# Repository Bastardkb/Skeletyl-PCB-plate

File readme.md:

# Skeletyl PCB - plate

Flexible PCB made for the Skeletyl.

With per-key RGB.

This repository contains all files necessary to order a PCB.

If you want to modify the design files, the Kicad sources are included.
If you just want to order the PCBs, check out the Release section which contain the gerber files.

## How to order

Order with a 0.6mm or 0.8mm PCB thickness

## License

Licensed under CC BY-NC-SA 4.0
Copyright Quentin Lebastard 2021

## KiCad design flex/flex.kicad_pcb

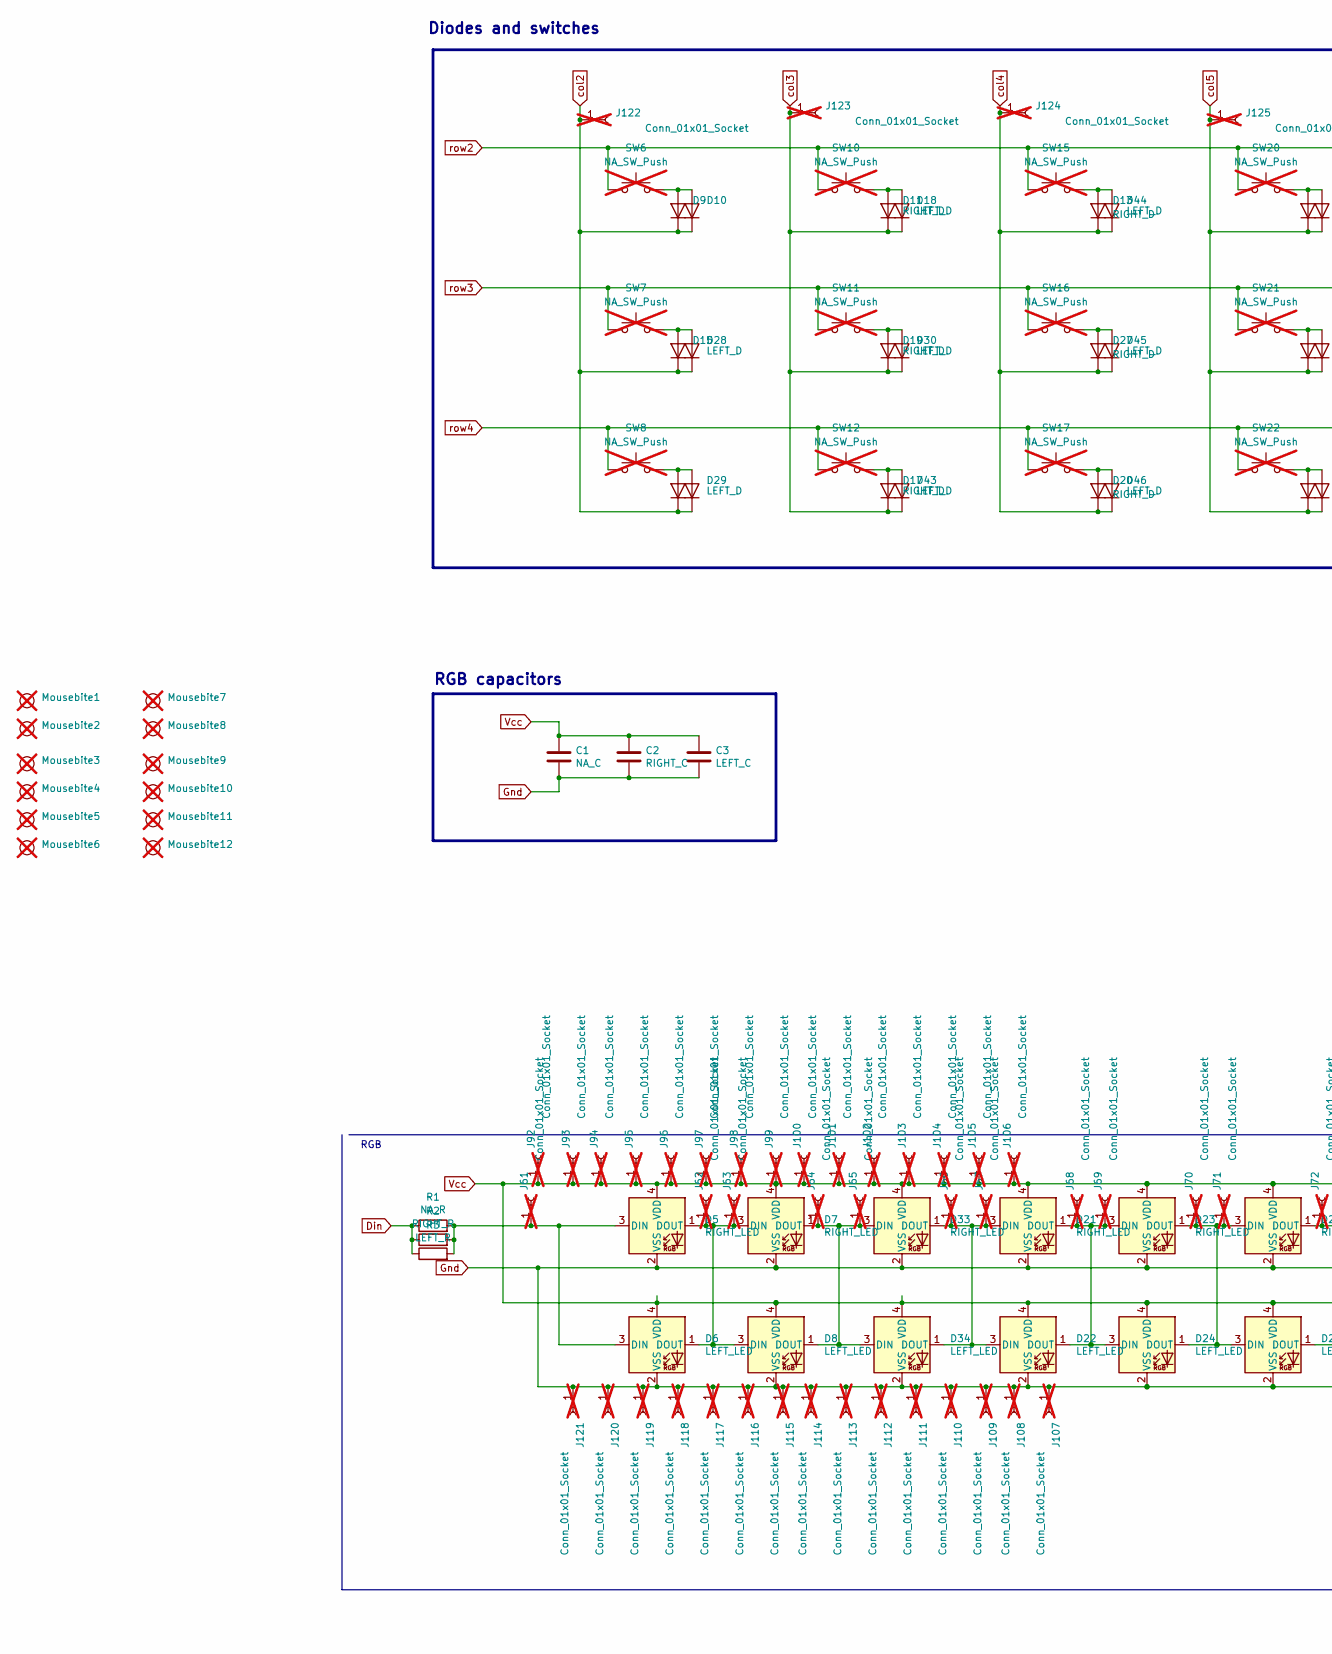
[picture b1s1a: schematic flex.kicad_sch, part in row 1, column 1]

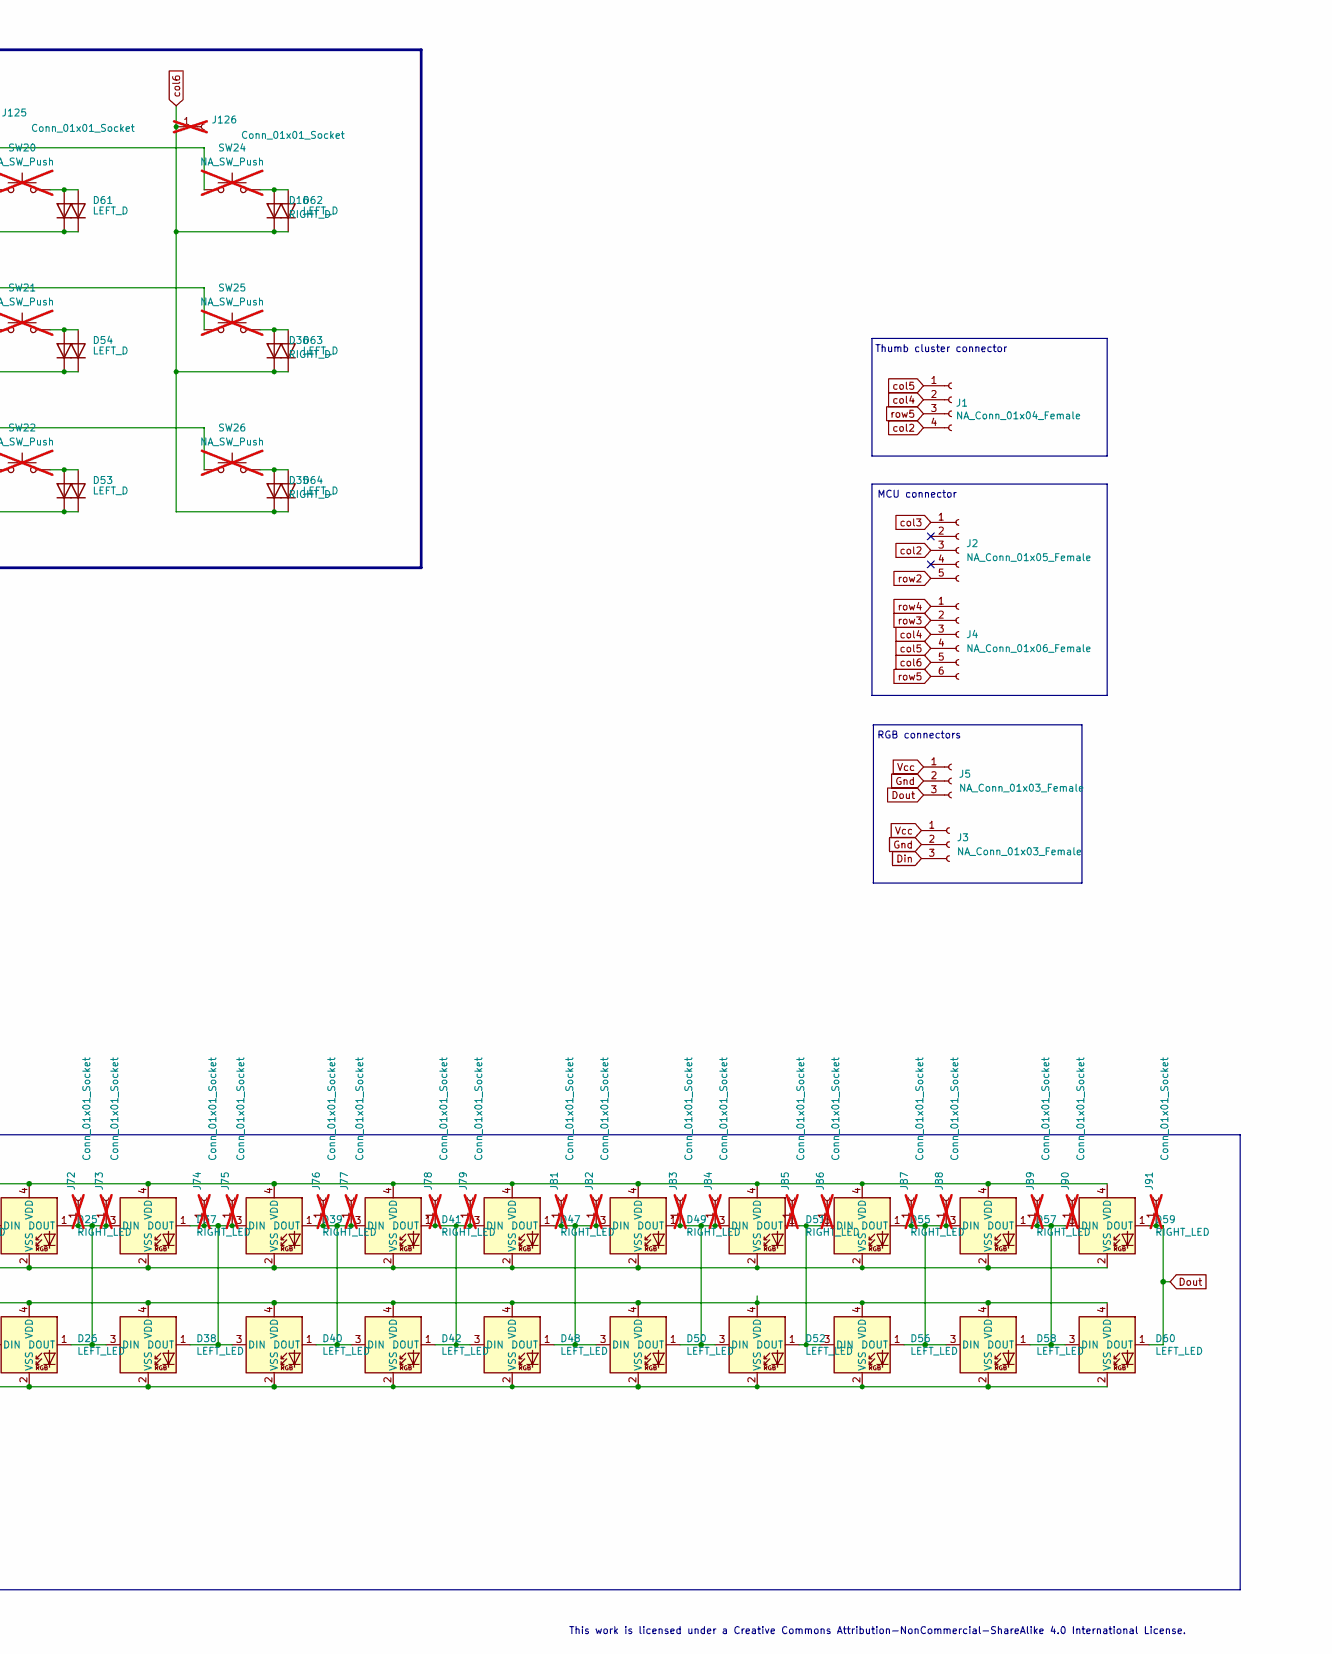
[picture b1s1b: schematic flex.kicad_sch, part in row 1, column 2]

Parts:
C1: NA_C; C_1206_3216Metric_Pad1.33x1.80mm_HandSolder_reversible
C2: RIGHT_C; R_0402
C3: LEFT_C; R_0402
D5, D7, D21, D23, D25, D33, D37, D39, D41, D47, D49, D51, D55, D57, D59: RIGHT_LED; SK6812_mini_e_corners
D6, D8, D22, D24, D26, D34, D38, D40, D42, D48, D50, D52, D56, D58, D60: LEFT_LED; SK6812_mini_e_corners_noedgecuts
D9, D11, D12, D13, D14, D15, D16, D17, D19, D20, D27, D31, D32, D35, D36: RIGHT_D; SOD123_assembly
D10, D18, D28, D29, D30, D43, D44, D45, D46, D53, D54, D61, D62, D63, D64: LEFT_D; SOD123_assembly
J1: NA_Conn_01x04_Female; PinHeader_1x04_P2.54mm_Vertical
J2: NA_Conn_01x05_Female; PinHeader_1x05_P2.54mm_Vertical
J3, J5: NA_Conn_01x03_Female; PinHeader_1x03_P2.54mm_Vertical
J4: NA_Conn_01x06_Female; PinHeader_1x06_P2.54mm_Vertical
J61, J63, J65, J67, J69, J71, J73, J75, J77, J79, J82, J84, J86, J88, J90: Conn_01x01_Socket; PinHeader_1x01_P1.27mm_Vertical_IN; not fitted
J62, J64, J66, J68, J70, J72, J74, J76, J78, J81, J83, J85, J87, J89, J91: Conn_01x01_Socket; PinHeader_1x01_P1.27mm_Vertical_OUT; not fitted
J92, J93, J94, J95, J96, J97, J98, J99, J100, J101, J102, J103, J104, J105, J106: Conn_01x01_Socket; PinHeader_1x01_P1.27mm_Vertical_VCC; not fitted
J107, J108, J109, J110, J111, J112, J113, J114, J115, J116, J117, J118, J119, J120, J121: Conn_01x01_Socket; PinHeader_1x01_P1.27mm_Vertical_GND; not fitted
J122, J123, J124, J125, J126: Conn_01x01_Socket; PinHeader_1x01_P1.27mm_Vertical; not fitted
Mousebite1, Mousebite2, Mousebite3, Mousebite4, Mousebite5, Mousebite6, Mousebite7, Mousebite8, Mousebite9, Mousebite10, Mousebite11, Mousebite12: mousebite; not fitted
R1: NA_R; R_1206_3216Metric_Pad1.30x1.75mm_HandSolder_reversible
R2: RIGHT_R; R_0402
R3: LEFT_R; R_0402
SW6, SW7, SW8, SW10, SW11, SW12, SW15, SW16, SW17, SW20, SW21, SW22, SW24, SW25, SW26: NA_SW_Push; SW_MX_reversible; not fitted

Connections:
Din: J3.3, R1.1, R2.1, R3.1
Dout: D59.1 (DOUT), D60.1 (DOUT), J5.3, J91.1
Gnd: C1.2, C2.2, C3.2, D5.2 (VSS), D6.2 (VSS), D7.2 (VSS), D8.2 (VSS), D21.2 (VSS), D22.2 (VSS), D23.2 (VSS), D24.2 (VSS), D25.2 (VSS), D26.2 (VSS), D33.2 (VSS), D34.2 (VSS), D37.2 (VSS), D38.2 (VSS), D39.2 (VSS), D40.2 (VSS), D41.2 (VSS), D42.2 (VSS), D47.2 (VSS), D48.2 (VSS), D49.2 (VSS), D50.2 (VSS), D51.2 (VSS), D52.2 (VSS), D55.2 (VSS), D56.2 (VSS), D57.2 (VSS), D58.2 (VSS), D59.2 (VSS), D60.2 (VSS), J3.2, J5.2, J107.1, J108.1, J109.1, J110.1, J111.1, J112.1, J113.1, J114.1, J115.1, J116.1, J117.1, J118.1, J119.1, J120.1, J121.1
unnamed: D5.3 (DIN), D6.3 (DIN), J61.1, R1.2, R2.2, R3.2
unnamed: D5.1 (DOUT), D6.1 (DOUT), D7.3 (DIN), D8.3 (DIN), J62.1, J63.1
unnamed: D9.2 (A), D10.2 (A), SW6.2
unnamed: D11.2 (A), D18.2 (A), SW10.2
unnamed: D12.2 (A), D29.2 (A), SW8.2
unnamed: D13.2 (A), D44.2 (A), SW15.2
unnamed: D14.2 (A), D61.2 (A), SW20.2
unnamed: D15.2 (A), D28.2 (A), SW7.2
unnamed: D16.2 (A), D62.2 (A), SW24.2
unnamed: D17.2 (A), D43.2 (A), SW12.2
unnamed: D19.2 (A), D30.2 (A), SW11.2
unnamed: D20.2 (A), D46.2 (A), SW17.2
unnamed: D21.3 (DIN), D22.3 (DIN), D33.1 (DOUT), D34.1 (DOUT), J66.1, J67.1
unnamed: D21.1 (DOUT), D22.1 (DOUT), D23.3 (DIN), D24.3 (DIN), J68.1, J69.1
unnamed: D23.1 (DOUT), D24.1 (DOUT), D25.3 (DIN), D26.3 (DIN), J70.1, J71.1
unnamed: D25.1 (DOUT), D26.1 (DOUT), D37.3 (DIN), D38.3 (DIN), J72.1, J73.1
unnamed: D27.2 (A), D45.2 (A), SW16.2
unnamed: D31.2 (A), D53.2 (A), SW22.2
unnamed: D32.2 (A), D54.2 (A), SW21.2
unnamed: D7.1 (DOUT), D8.1 (DOUT), D33.3 (DIN), D34.3 (DIN), J64.1, J65.1
unnamed: D35.2 (A), D64.2 (A), SW26.2
unnamed: D36.2 (A), D63.2 (A), SW25.2
unnamed: D37.1 (DOUT), D38.1 (DOUT), D39.3 (DIN), D40.3 (DIN), J74.1, J75.1
unnamed: D39.1 (DOUT), D40.1 (DOUT), D41.3 (DIN), D42.3 (DIN), J76.1, J77.1
unnamed: D41.1 (DOUT), D42.1 (DOUT), D47.3 (DIN), D48.3 (DIN), J78.1, J79.1
unnamed: D47.1 (DOUT), D48.1 (DOUT), D49.3 (DIN), D50.3 (DIN), J81.1, J82.1
unnamed: D49.1 (DOUT), D50.1 (DOUT), D51.3 (DIN), D52.3 (DIN), J83.1, J84.1
unnamed: D51.1 (DOUT), D52.1 (DOUT), D55.3 (DIN), D56.3 (DIN)
unnamed: D55.1 (DOUT), D56.1 (DOUT), D57.3 (DIN), D58.3 (DIN), J87.1, J88.1
unnamed: D57.1 (DOUT), D58.1 (DOUT), D59.3 (DIN), D60.3 (DIN), J89.1
Vcc: C1.1, C2.1, C3.1, D5.4 (VDD), D6.4 (VDD), D7.4 (VDD), D8.4 (VDD), D21.4 (VDD), D22.4 (VDD), D23.4 (VDD), D24.4 (VDD), D25.4 (VDD), D26.4 (VDD), D33.4 (VDD), D34.4 (VDD), D37.4 (VDD), D38.4 (VDD), D39.4 (VDD), D40.4 (VDD), D41.4 (VDD), D42.4 (VDD), D47.4 (VDD), D48.4 (VDD), D49.4 (VDD), D50.4 (VDD), D51.4 (VDD), D52.4 (VDD), D55.4 (VDD), D56.4 (VDD), D57.4 (VDD), D58.4 (VDD), D59.4 (VDD), D60.4 (VDD), J3.1, J5.1, J92.1, J93.1, J94.1, J95.1, J96.1, J97.1, J98.1, J99.1, J100.1, J101.1, J102.1, J103.1, J104.1, J105.1, J106.1
col2: D9.1 (K), D10.1 (K), D12.1 (K), D15.1 (K), D28.1 (K), D29.1 (K), J1.4, J2.3, J122.1
col3: D11.1 (K), D17.1 (K), D18.1 (K), D19.1 (K), D30.1 (K), D43.1 (K), J2.1, J123.1
col4: D13.1 (K), D20.1 (K), D27.1 (K), D44.1 (K), D45.1 (K), D46.1 (K), J1.2, J4.3, J124.1
col5: D14.1 (K), D31.1 (K), D32.1 (K), D53.1 (K), D54.1 (K), D61.1 (K), J1.1, J4.4, J125.1
col6: D16.1 (K), D35.1 (K), D36.1 (K), D62.1 (K), D63.1 (K), D64.1 (K), J4.5, J126.1
row2: J2.5, SW6.1, SW10.1, SW15.1, SW20.1, SW24.1
row3: J4.2, SW7.1, SW11.1, SW16.1, SW21.1, SW25.1
row4: J4.1, SW8.1, SW12.1, SW17.1, SW22.1, SW26.1
row5: J1.3, J4.6

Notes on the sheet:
RGB connectors
MCU connector
Thumb cluster connector
RGB capacitors
Diodes and switches
RGB
This work is licensed under a Creative Commons Attribution-NonCommercial-ShareAlike 4.0 International License.

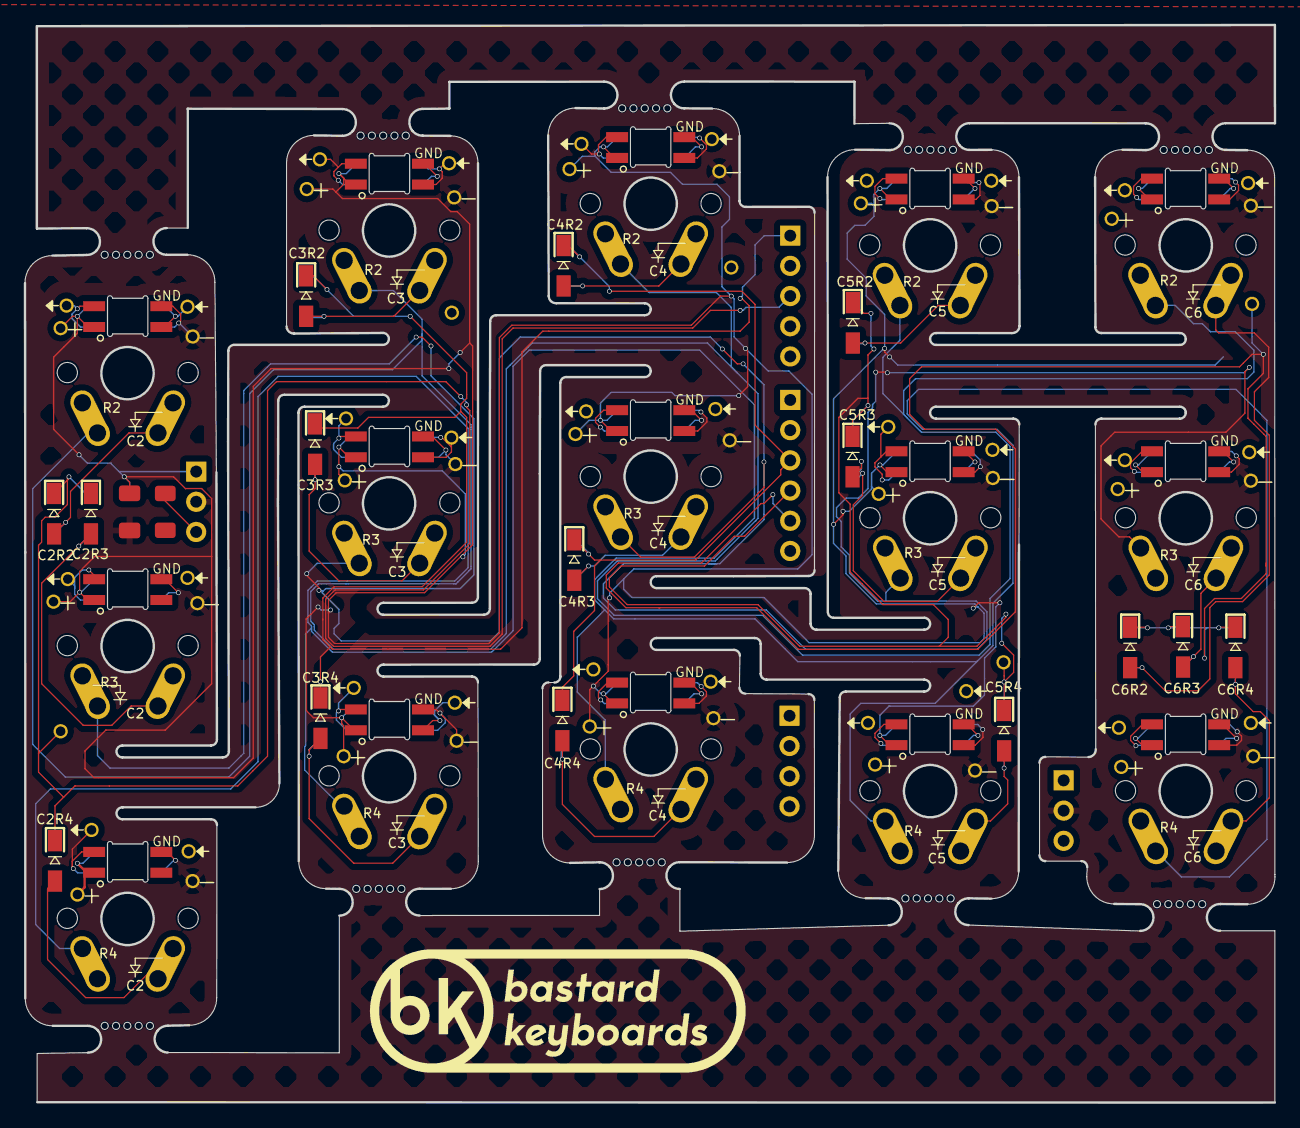
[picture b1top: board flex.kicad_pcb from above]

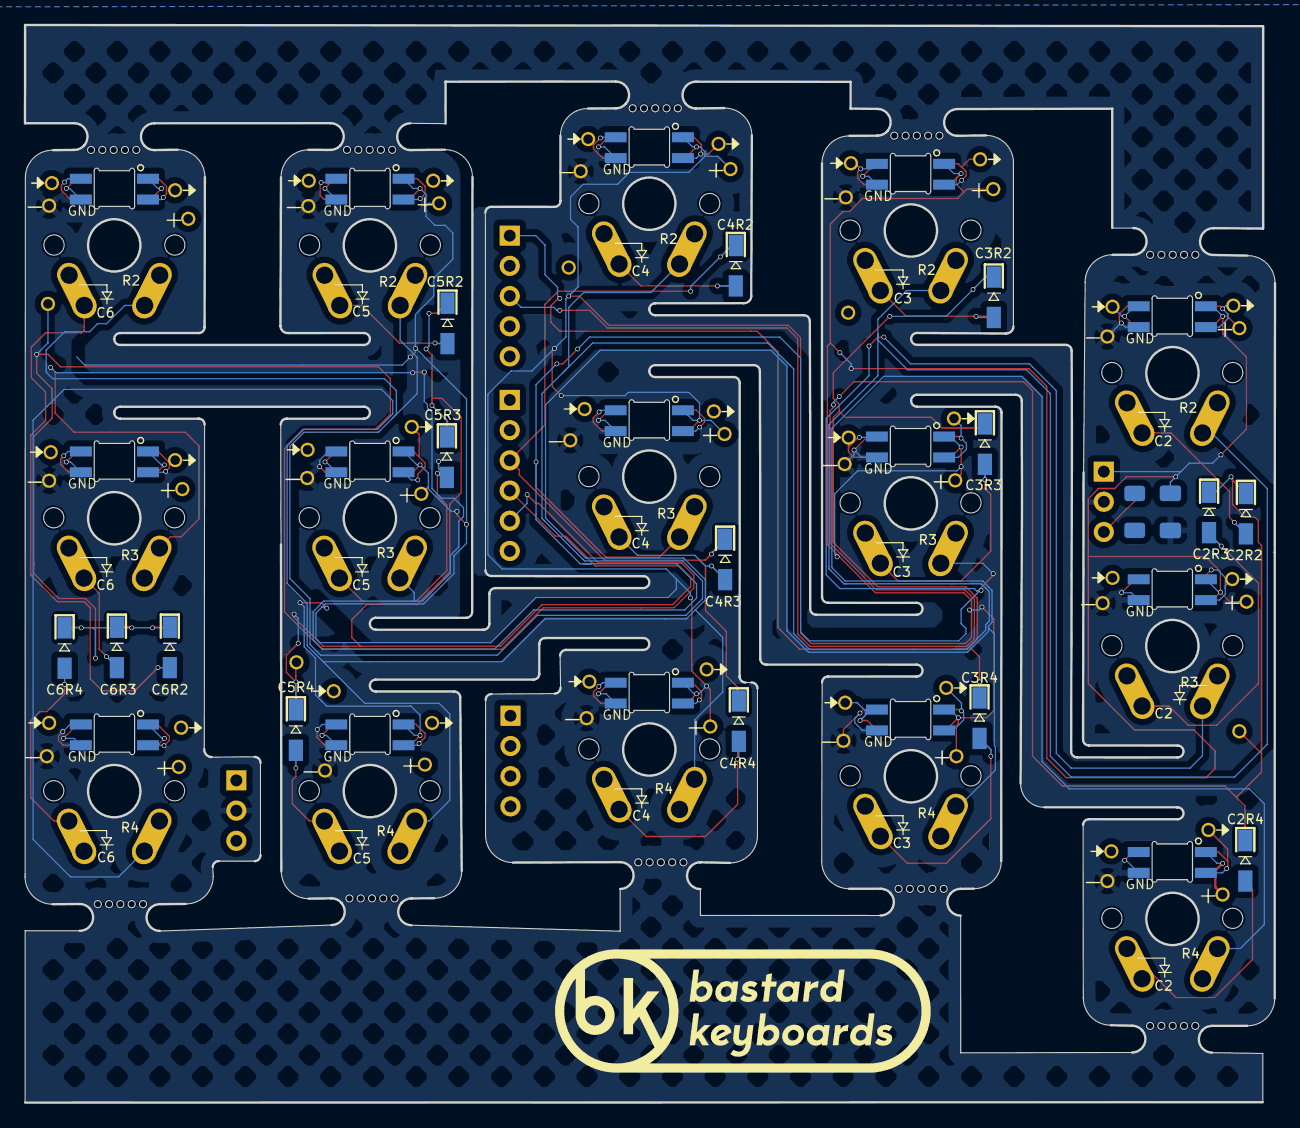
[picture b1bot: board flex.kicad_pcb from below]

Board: 2 copper layers, 105.1 x 90.6 mm, 159 parts (46 on the bottom side), 43 nets.

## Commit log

2022-01-24 add stuff
2022-01-24 licenses
2023-04-20 edge cuts
2023-04-20 PCB settigs
2023-05-16 cleanup schem, reversible r and c
2023-05-16 place smd components
2023-05-23 change LEDs
2023-05-23 routing
2023-05-29 routing, bom
2023-05-29 move diodes
2023-05-29 move capacitor label
2023-05-30 move first col diodes
2023-05-30 silkscreen
2023-08-15 bigger switch holes
2023-08-15 rounder corner on connector
2023-10-02 widerflex connector
2023-10-02 hatched zones
2023-10-02 double connections around C4R4
2023-10-02 zones, version number
2023-10-02 fix clearances
2023-11-02 update diode silkscreens
2023-11-17 silkscreen version etc
2024-12-06 move top edge cuts for led
2025-08-12 footprint work
2025-08-12 more footprint work
2025-08-20 place LEDs
2025-08-20 remove small diodes
2025-08-20 stronger flextrip connector
2025-08-28 update diode footprints
2025-08-28 place diodes
2025-09-02 add mouse bite footprints
2025-09-02 stronger inner column bridge
2025-09-02 zone hatch fill
2025-09-02 add rowcol silkscreen
2025-09-02 work
2025-09-03 update LEDs
2025-09-03 diode labels
2025-09-03 logo
2025-09-03 add LED in/out/vcc/gnd connectors
2025-09-05 place breakouts
2025-09-12 place led breakouts
2025-10-31 routing VCC

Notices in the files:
flex/flex.kicad_pcb:
Copyright Quentin Lebastard 2023
flex/flex.kicad_sch:
Copyright Quentin Lebastard 2022
